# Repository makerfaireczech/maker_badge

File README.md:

# Maker badge
The Maker badge board is the official badge board for Maker Faire's in the Czech republic. The main purpose is to show visitors/exhibitors name and/or project, but the secondary goal is to have at each Maker Faire some interactive game so people can have more fun at the time of the visit.

This board supports [Arduino](https://github.com/espressif/arduino-esp32) and [CircuitPython](https://learn.adafruit.com/welcome-to-circuitpython) platform. 

CircuitPython will be **primary** platform for this board because it is very easy to use, and anybody who will buy a board at some Maker Fair should be able very easily change (at least) her/his name on the display, so anybody knows the name of the person when they start chatting about something.  

I will try to add as many examples for both platforms, as I could, but I already saw few very interesting projects.

## How to use this board in 5 steps:  

1) Connect USB-C cable to the board and turn it on. 
Either use a slide switch (top = OFF, down = ON) or move the jumper to the middle pins. This depends on the version which you have. 

2) Locate drive name "**Circuitpy**" and open **code.py** in some text editor. 
We recommend using **Mu editor**, but even Notepad will work. 

3) Find a line where is **"Jmeno"** (Name), **"Prijmeni"** (Surname), **"Firma/Projekt"** (Company/Project) and change it to whatever suit your need. 
There is yet no "auto aligning", so you have to also change X & Y coordinates for particular text. 

4) Save it via **CTRL+S/CMD+S** or you application menu for that. If the screen does not refresh, push the RESET button. 

5) Unplug the USB cable, put the strap around your neck, and wear it with pride. 

## Board version

There are currently following revisions of the board:

- rev. A : this version was distributed by me and it was using **212 x 104 px** e-ink display with UC8151D driver
- rev. B : this board was assembled by me for Maker Faire Prague 2022 and it was using **250 x 122 px** e-ink display with SSD1680 driver from Make More. It contains the same type of components as rev. A .  
- rev. C (with rev. B markings at the back): this board was assembled by PCBWay and it was using **250 x 122 px** e-ink display with SSD1680 driver from Make More. Some of the components are different because the original parts were not available due to chip shortage. These boards were distributed between Maker Faire Brno 2022 (22 - 23/10/2022) and Maker Faire Prague 2023 (10 - 11/6/2023).
- rev. D : this board was assembled by PCBWay and it contains these changes:
	- slide switch for power control instead of jumper over pins
	- transistor at e-ink display power line to save power 
	- transistor at resistor divider for battery measuring
	- CR2032 holder was removed to save the cost of the board

	These boards were distributed at Maker Faire Prague 2023 (10 - 11/6/2023) and onwards.

## Where can you buy it? 

[Makermarket](https://www.makermarket.cz/maker-badge)

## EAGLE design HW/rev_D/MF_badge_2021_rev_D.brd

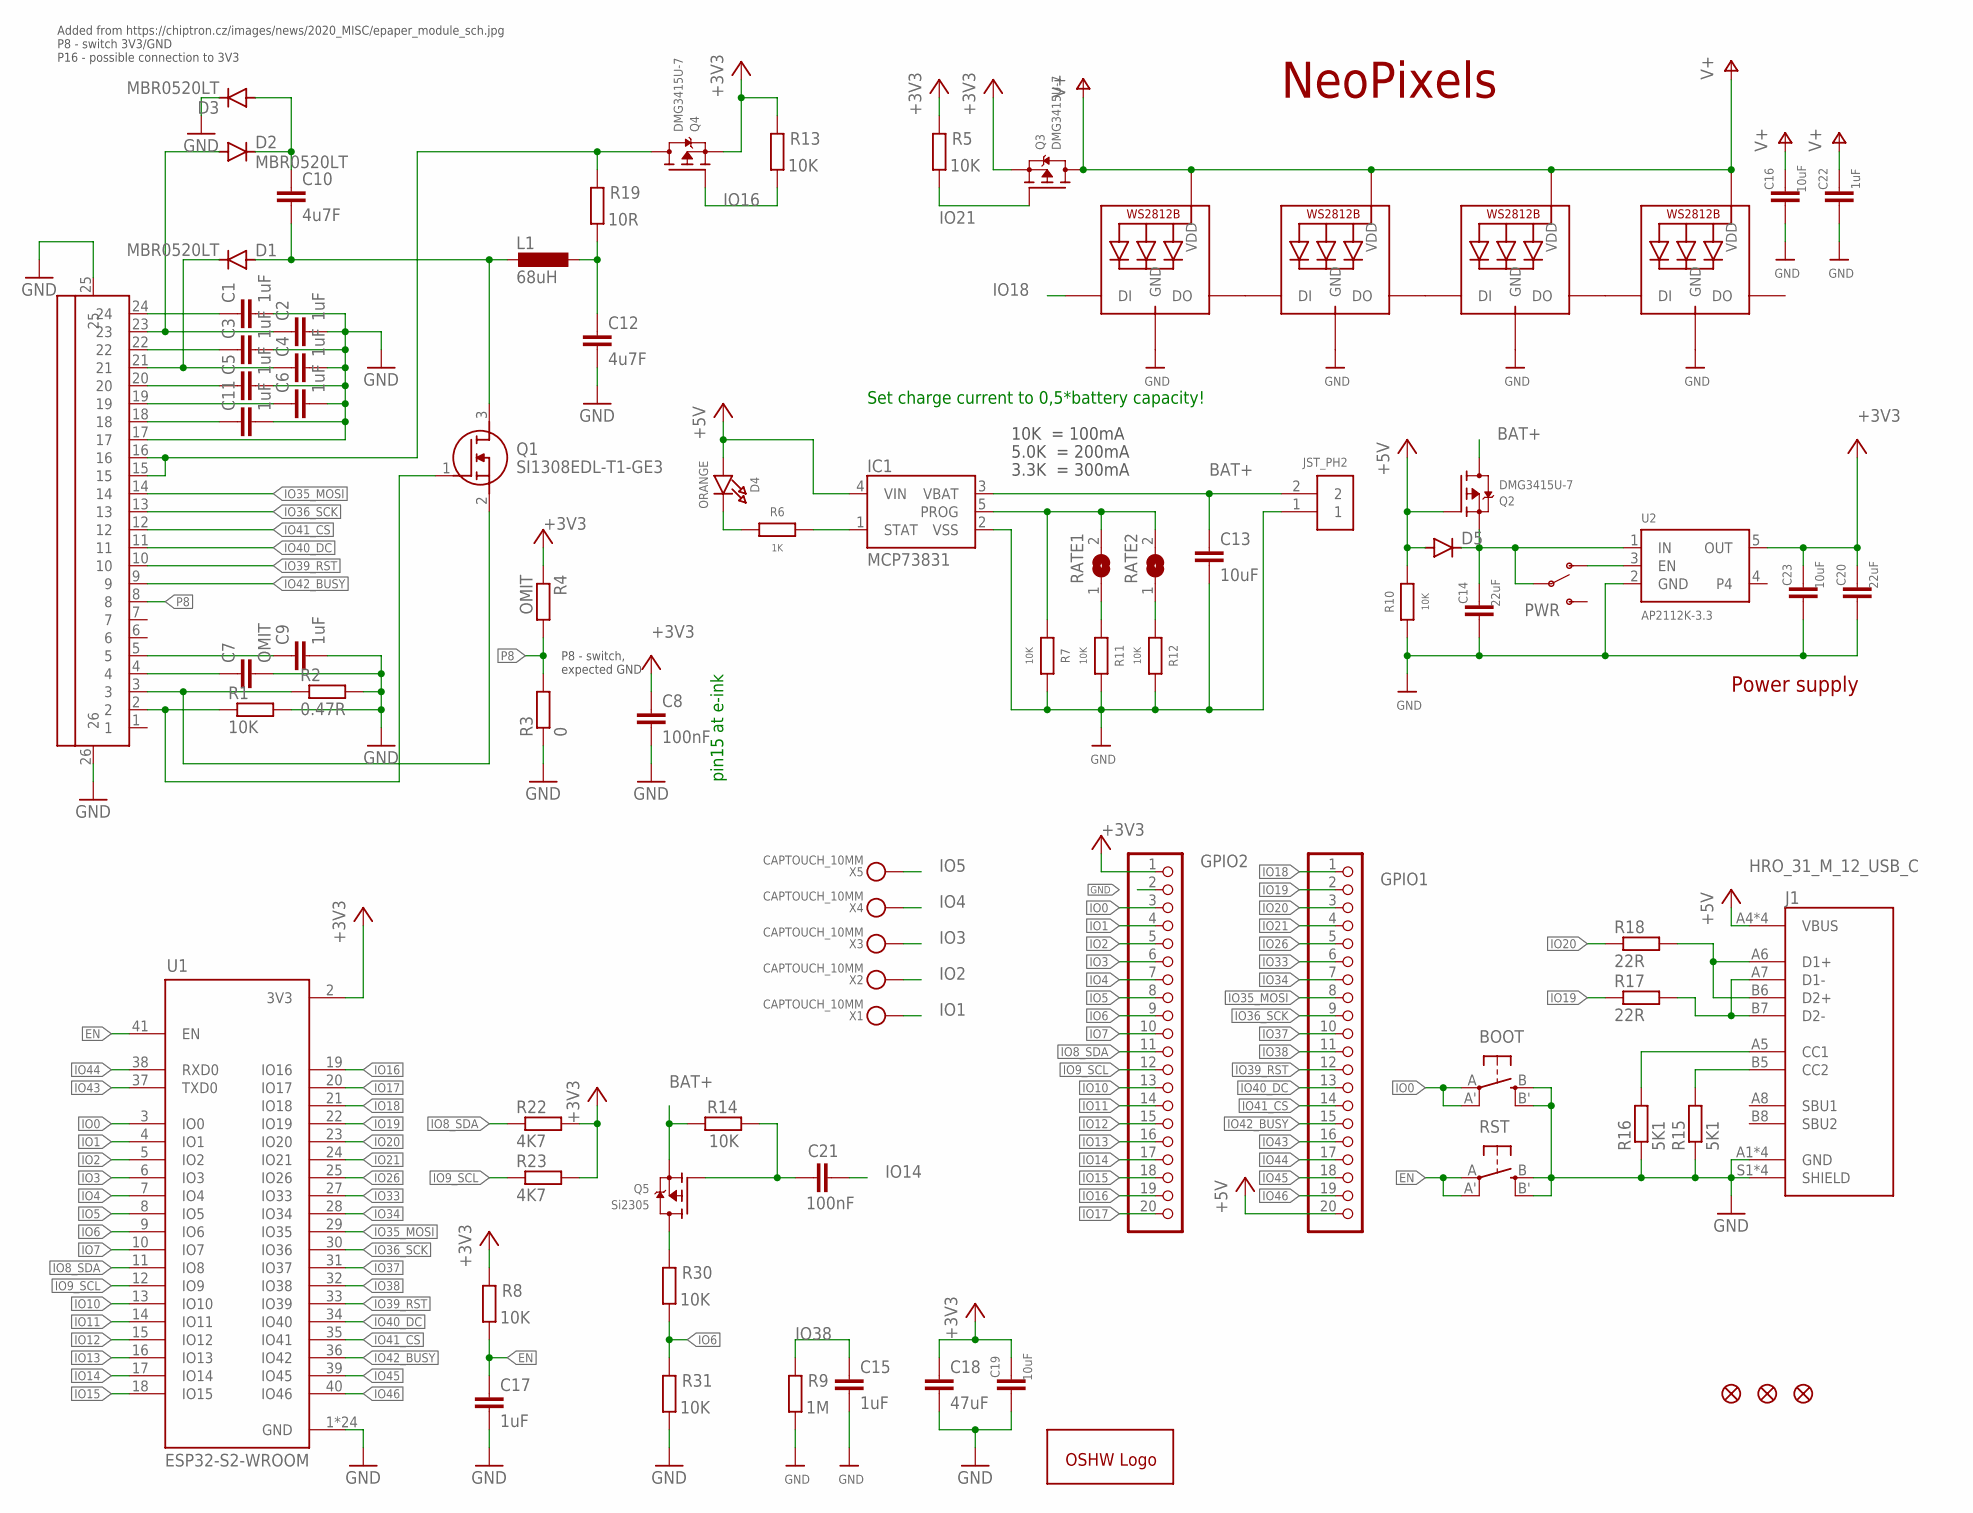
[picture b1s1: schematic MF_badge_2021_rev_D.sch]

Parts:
BOOT: BUTTON_KMR2_4.6X2.8
C1, C2, C3, C4, C5, C6, C9, C11, C15, C17, C22: 1uF; C0805
C7: OMIT; C0805
C8, C21: 100nF; C0805
C10, C12: 4u7F; C0805
C13, C16, C19, C23: 10uF; C0805
C14, C20: 22uF; C0805
C18: 47uF; C0805
D1, D2, D3, D5: MBR0520LT; SOD123
D4: ORANGE; CHIPLED_0805_NOOUTLINE
FID1, FID2, FID3: FIDUCIAL""; FIDUCIAL_1MM
GOLD_ORB_SM1: OSHWLOGO_; OSHW_5MM_LOGO
GPIO1, GPIO2: PINHD-1X20; 1X20
IC1: MCP73831; SOT95P290X120-5
J1: HRO_31_M_12_USB_C
L1: 68uH; L4532P
LED2, LED3, LED4, LED5: WS2812B5050; WS2812B
PWR: SWITCH-SPDT-SMD-RIGHT-ANGLE; SWITCH_SPST_SMD_A
Q1: SI1308EDL-T1-GE3; SOT65P210X110-3N
Q2, Q3, Q4: DMG3415U-7; SOT23-R
Q5: Si2305; SOT23-R
R1, R5, R7, R8, R10, R11, R12, R13, R14, R30, R31: 10K; R0805
R2: 0.47R; R0805
R3: 0; R0805
R4: OMIT; R0805
R6: 1K; R0805
R9: 1M; R0805
R15, R16: 5K1; R0805
R17, R18: 22R; R0805
R19: 10R; R0805
R22, R23: 4K7; R0805
RATE1, RATE2: SOLDERJUMPER; SOLDERJUMPER_ARROW_NOPASTE
RST: BUTTON_KMR2_4.6X2.8
U1: ESP32-S2-WROOM; XCVR_ESP32-S2-WROOM
U2: AP2112K-3.3; SOT23-5
U$1: 2.13_EINK
U$8: JST_PH2; JSTPH2
X1, X2, X3, X4, X5: CAPTOUCH_10MM; CAPTOUCH_6X9MM

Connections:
+3V3: C8.1, C18.1, C19.1, C20.1, C23.1, GPIO2.1, Q3.2 (S), Q4.2 (S), R4.1, R5.2, R8.2, R13.2, R22.2, R23.2, U1.2 (3V3), U2.5 (OUT)
+5V: D4.A, D5.A, GPIO1.20, IC1.4 (VIN), J1.A4 (VBUS), J1.A9 (VBUS), J1.B4 (VBUS), J1.B9 (VBUS), Q2.1 (G), R10.2
BAT+: C13.1, IC1.3 (VBAT), Q2.3 (D), Q5.2 (S), R14.2, U$8.2
D+_CON: J1.A6 (D1+), J1.B6 (D2+), R18.2
D-_CON: J1.A7 (D1-), J1.B7 (D2-), R17.2
EN: C17.1, R8.1, RST.A, RST.A' (P1), U1.41 (EN)
GND: BOOT.B (S), BOOT.B' (S1), C1.2, C2.2, C3.2, C4.2, C5.2, C6.2, C7.2, C8.2, C9.2, C11.2, C12.2, C13.2, C14.2, C15.2, C16.2, C17.2, C18.2, C19.2, C20.2, C22.2, C23.2, D3.C, GPIO2.2, IC1.2 (VSS), J1.A1 (GND), J1.A12 (GND), J1.B1 (GND), J1.B12 (GND), J1.S1 (SHIELD), J1.S2 (SHIELD), J1.S3 (SHIELD), J1.S4 (SHIELD), LED2.3-GND (GND), LED3.3-GND (GND), LED4.3-GND (GND), LED5.3-GND (GND), R1.2, R2.2, R3.1, R7.2, R9.1, R10.1, R11.2, R12.2, R15.1, R16.1, R31.1, RST.B (S), RST.B' (S1), U1.1 (GND), U1.26 (GND), U1.42 (GND), U1.43.1 (GND), U1.43.2 (GND), U1.43.3 (GND), U1.43.4 (GND), U1.43.5 (GND), U1.43.6 (GND), U1.43.7 (GND), U1.43.8 (GND), U1.43.9 (GND), U1.43.10 (GND), U1.43.11 (GND), U1.43.12 (GND), U1.43.13 (GND), U1.43.14 (GND), U1.43.15 (GND), U1.43.16 (GND), U1.43.17 (GND), U1.43.18 (GND), U1.43.19 (GND), U1.43.20 (GND), U1.43.21 (GND), U2.2 (GND), U$1.17, U$1.25, U$1.26, U$8.1
IO0: BOOT.A, BOOT.A' (P1), GPIO2.3, U1.3 (IO0)
IO1: GPIO2.4, U1.4 (IO1), X1.P$1
IO2: GPIO2.5, U1.5 (IO2), X2.P$1
IO3: GPIO2.6, U1.6 (IO3), X3.P$1
IO4: GPIO2.7, U1.7 (IO4), X4.P$1
IO5: GPIO2.8, U1.8 (IO5), X5.P$1
IO6: GPIO2.9, R30.1, R31.2, U1.9 (IO6)
IO7: GPIO2.10, U1.10 (IO7)
IO8_SDA: GPIO2.11, R22.1, U1.11 (IO8)
IO9_SCL: GPIO2.12, R23.1, U1.12 (IO9)
IO10: GPIO2.13, U1.13 (IO10)
IO11: GPIO2.14, U1.14 (IO11)
IO12: GPIO2.15, U1.15 (IO12)
IO13: GPIO2.16, U1.16 (IO13)
IO14: C21.2, GPIO2.17, U1.17 (IO14)
IO15: GPIO2.18, U1.18 (IO15)
IO16: GPIO2.19, Q4.1 (G), R13.1, U1.19 (IO16)
IO17: GPIO2.20, U1.20 (IO17)
IO18: GPIO1.1, LED2.4-DIN (DI), U1.21 (IO18)
IO19: GPIO1.2, R17.1, U1.22 (IO19)
IO20: GPIO1.3, R18.1, U1.23 (IO20)
IO21: GPIO1.4, Q3.1 (G), R5.1, U1.24 (IO21)
IO26: GPIO1.5, U1.25 (IO26)
IO33: GPIO1.6, U1.27 (IO33)
IO34: GPIO1.7, U1.28 (IO34)
IO35_MOSI: GPIO1.8, U1.29 (IO35), U$1.14
IO36_SCK: GPIO1.9, U1.30 (IO36), U$1.13
IO37: GPIO1.10, U1.31 (IO37)
IO38: C15.1, GPIO1.11, R9.2, U1.32 (IO38)
IO39_RST: GPIO1.12, U1.33 (IO39), U$1.10
IO40_DC: GPIO1.13, U1.34 (IO40), U$1.11
IO41_CS: GPIO1.14, U1.35 (IO41), U$1.12
IO42_BUSY: GPIO1.15, U1.36 (IO42), U$1.9
IO43: GPIO1.16, U1.37 (TXD0)
IO44: GPIO1.17, U1.38 (RXD0)
IO45: GPIO1.18, U1.39 (IO45)
IO46: GPIO1.19, U1.40 (IO46)
unnamed: C1.1, U$1.24
unnamed: C2.1, D2.A, U$1.23
unnamed: C3.1, U$1.22
unnamed: C4.1, D1.C, U$1.21
unnamed: C5.1, U$1.20
unnamed: C6.1, U$1.19
unnamed: C11.1, U$1.18
unnamed: IC1.1 (STAT), R6.2
unnamed: C14.1, D5.C, PWR.2, Q2.2 (S), U2.1 (IN)
unnamed: Q1.2 (S), R2.1, U$1.3
unnamed: C9.1, U$1.5
unnamed: C7.1, U$1.4
unnamed: Q1.1 (G), R1.1, U$1.2
unnamed: D4.C, R6.1
unnamed: C10.1, D2.C, D3.A
unnamed: LED2.2-DOUT (DO), LED3.4-DIN (DI)
unnamed: PWR.1 (O), U2.3 (EN)
unnamed: C10.2, D1.A, L1.2, Q1.3 (D)
unnamed: R11.1, RATE1.1
unnamed: R12.1, RATE2.1
unnamed: LED4.2-DOUT (DO), LED5.4-DIN (DI)
unnamed: J1.B5 (CC2), R15.2
unnamed: J1.A5 (CC1), R16.2
unnamed: LED3.2-DOUT (DO), LED4.4-DIN (DI)
unnamed: Q4.3 (D), R19.2, U$1.15, U$1.16
unnamed: C12.1, L1.1, R19.1
unnamed: Q5.3 (D), R30.2
unnamed: C21.1, Q5.1 (G), R14.1
P8: R3.2, R4.2, U$1.8
PROG: IC1.5 (PROG), R7.1, RATE1.2, RATE2.2
V+: C16.1, C22.1, LED2.1-VDD (VDD), LED3.1-VDD (VDD), LED4.1-VDD (VDD), LED5.1-VDD (VDD), Q3.3 (D)

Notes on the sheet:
P8 - switch, expected GND
Added from https://chiptron.cz/images/news/2020_MISC/epaper_module_sch.jpg P8 - switch 3V3/GND P16 - possible connection to 3V3
10K = 100mA
5.0K = 200mA
3.3K = 300mA
Set charge current to 0,5*battery capacity!
Power supply
pin15 at e-ink
NeoPixels

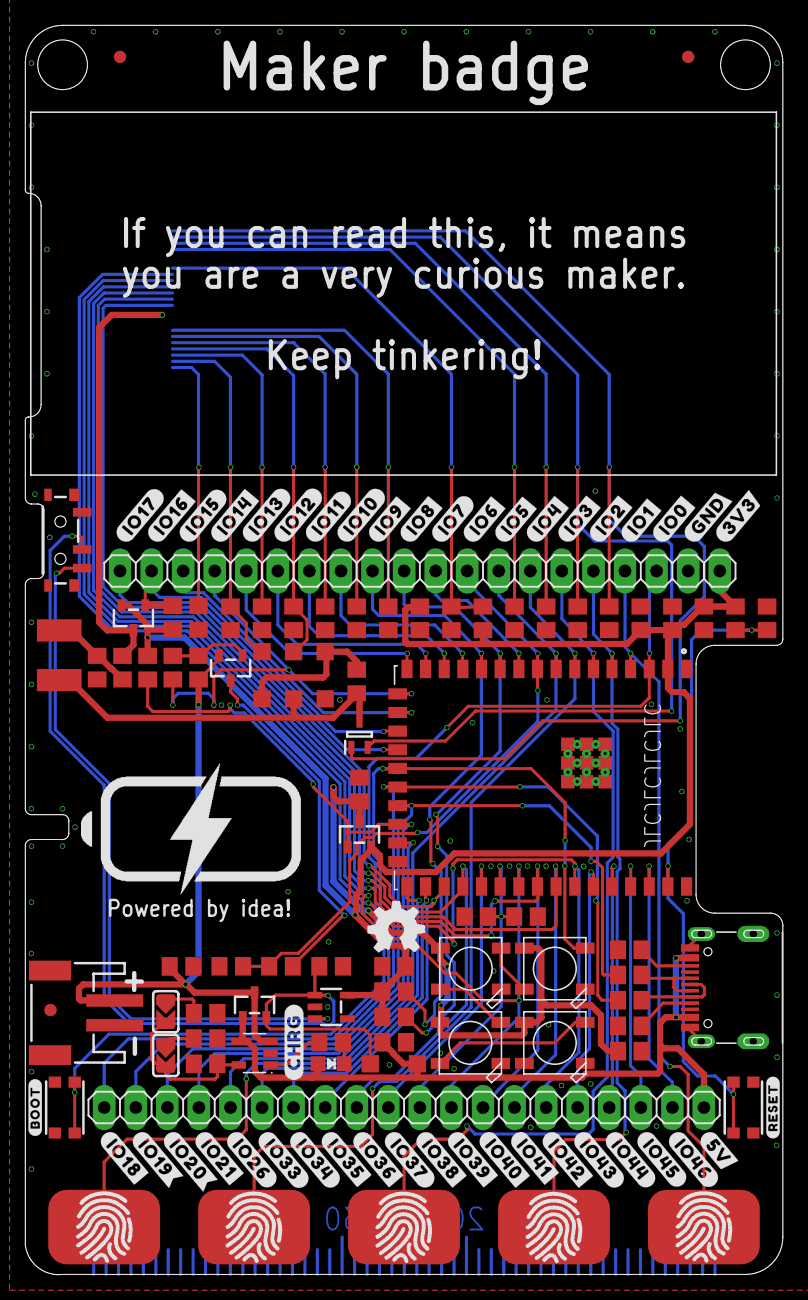
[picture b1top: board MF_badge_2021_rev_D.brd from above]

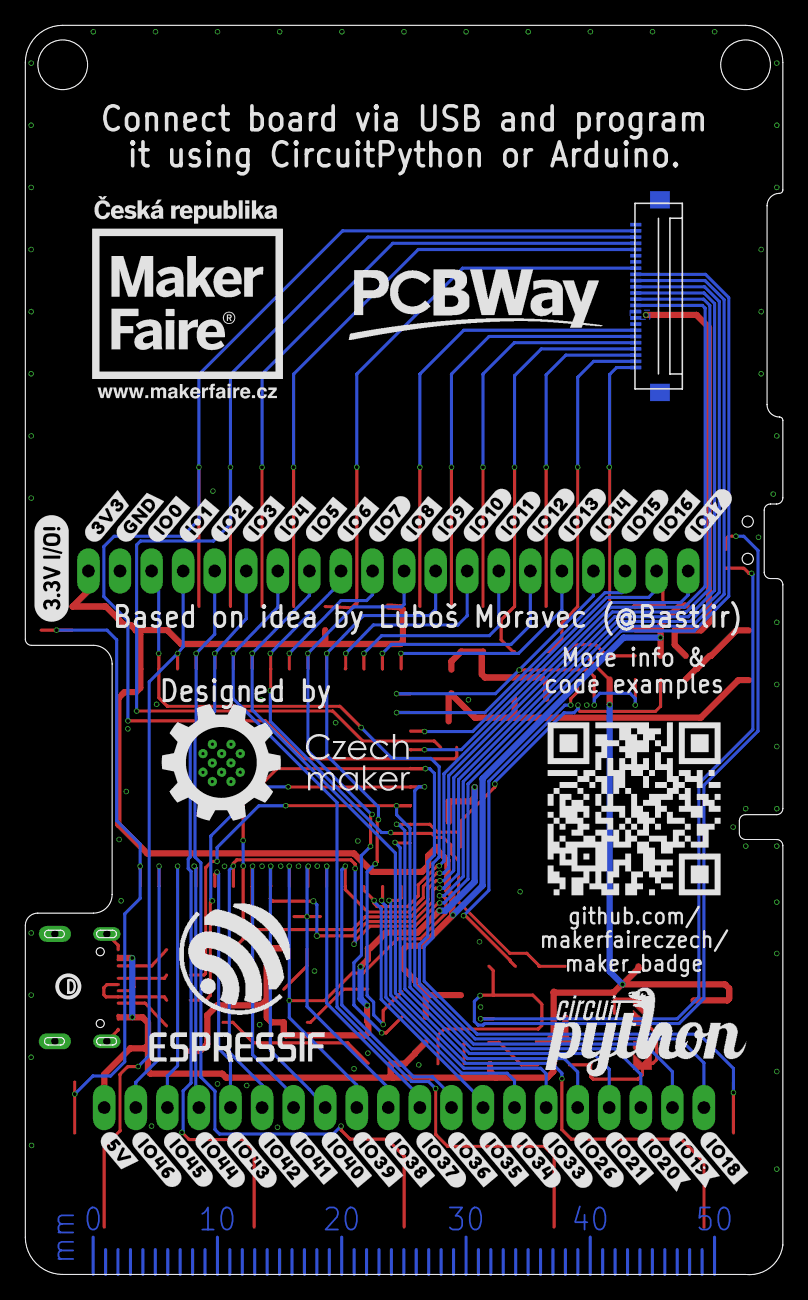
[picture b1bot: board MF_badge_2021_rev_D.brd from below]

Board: 2 copper layers, 61.0 x 100.5 mm, 167 parts (41 on the bottom side), 75 nets.

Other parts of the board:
U$2, U$92: #IO43#0
U$3, U$93: #IO44#0
U$4, U$33: #IO17#0
U$6, U$34: #IO16#0
U$7: #BOOT#0
U$9: #RESET#0
U$10: PCBFEAT-REV-040
U$12: #CHRG#0
U$16, U$77: #IO18#0
U$17, U$78: #IO19#0
U$18, U$79: #IO20#0
U$19, U$80: #IO21#0
U$20, U$81: #IO26#0
U$21, U$82: #IO33#0
U$22, U$83: #IO34#0
U$23, U$84: #IO35#0
U$24, U$85: #IO36#0
U$25, U$87: #IO38#0
U$26, U$86: #IO37#0
U$27, U$88: #IO39#0
U$28, U$89: #IO40#0
U$29, U$90: #IO41#0
U$30, U$91: #IO42#0
U$31, U$94: #IO45#0
U$32, U$95: #IO46#0
U$35, U$57: #IO15#0
U$37, U$58: #IO14#0
U$38, U$59: #IO13#0
U$39, U$60: #IO12#0
U$40, U$65: #IO11#0
U$41, U$66: #IO10#0
U$42, U$67: #IO9#0
U$43, U$68: #IO8#0
U$44, U$69: #IO7#0
U$45, U$70: #IO6#0
U$46, U$71: #IO5#0
U$47, U$72: #IO4#0
U$48, U$73: #IO3#0
U$49, U$74: #IO2#0
U$50, U$75: #IO1#0
U$51, U$76: #IO0#0
U$96, U$100: #GND#0
U$97, U$101: #3V3#0
U$98, U$99: #5V#0

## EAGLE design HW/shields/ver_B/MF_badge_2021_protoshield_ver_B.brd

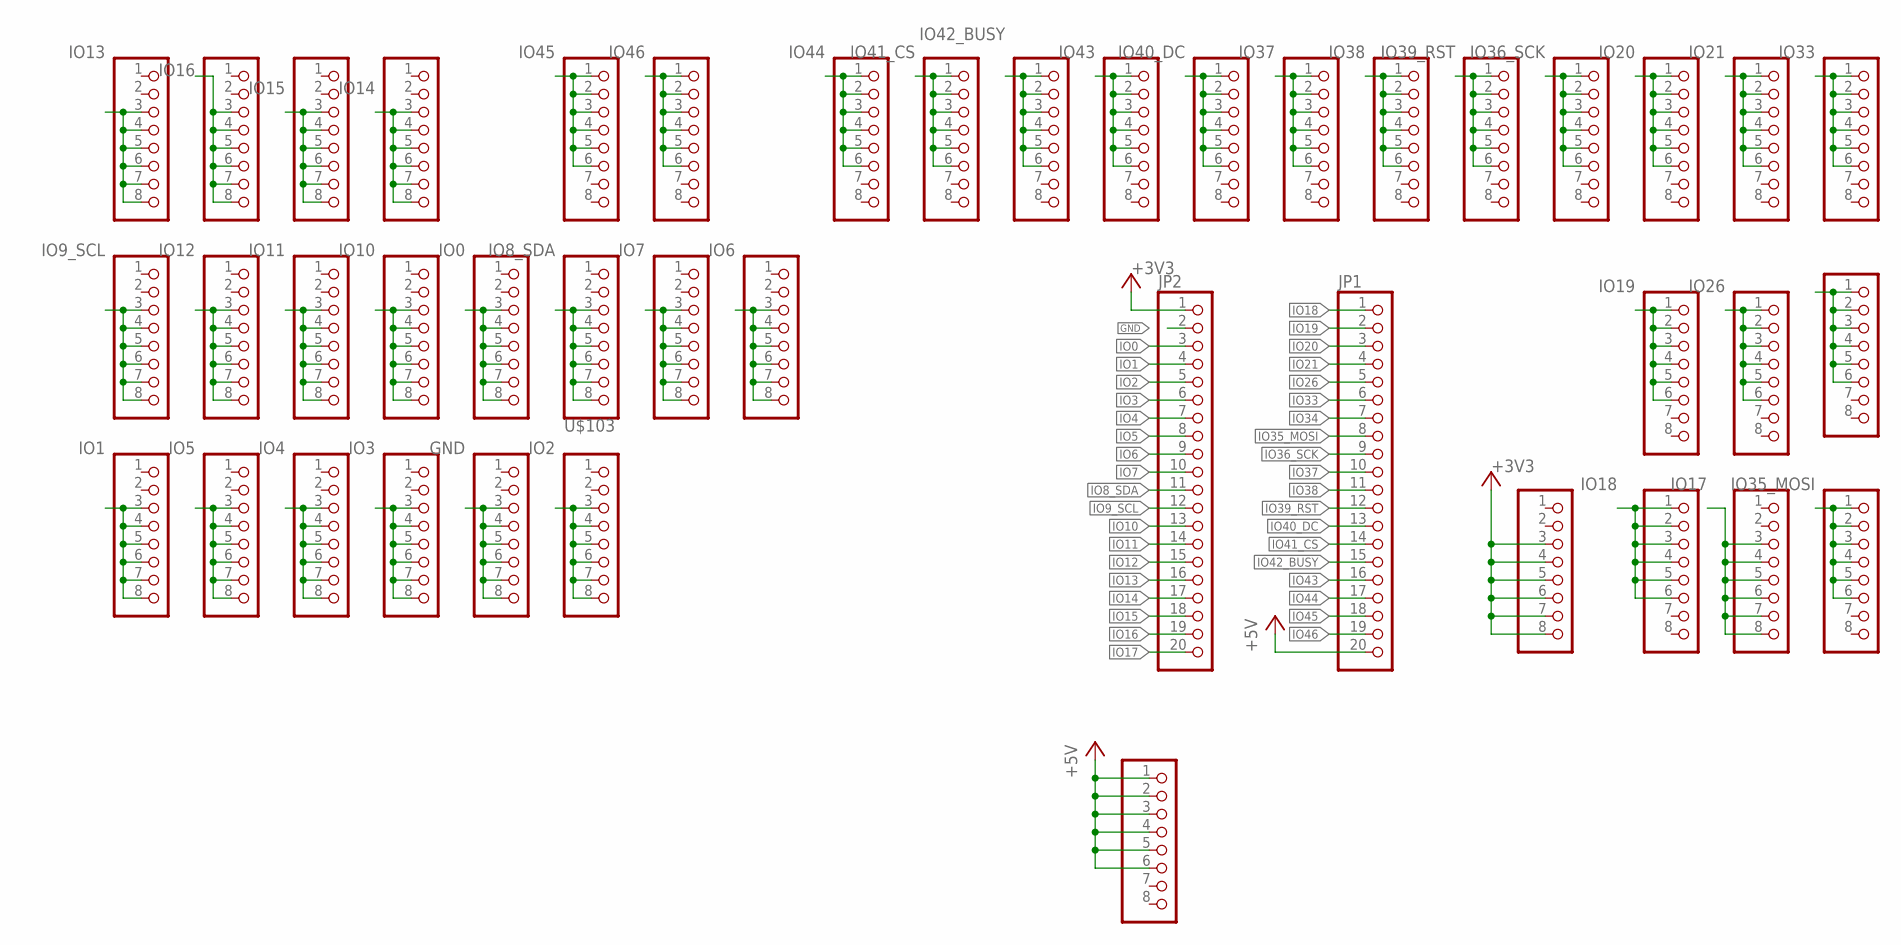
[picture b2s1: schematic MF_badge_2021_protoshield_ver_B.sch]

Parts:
JP1, JP2: PINHD-1X20_CLEANBIG; 1X20-CLEANBIG
U$1, U$5, U$7, U$8, U$9, U$10, U$11, U$12, U$13, U$14, U$15, U$36, U$52, U$53, U$54, U$55, U$56, U$61, U$62, U$63, U$64, U$102, U$103, U$104, U$105, U$106, U$107, U$108, U$109, U$110, U$111, U$112, U$113, U$114, U$115, U$116, U$117, U$118, U$119, U$120: PINHD-1X8CLEANBIG; 1X08-CLEANBIG

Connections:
+3V3: JP2.1, U$1.3, U$1.4, U$1.5, U$1.6, U$1.7, U$1.8
+5V: JP1.20, U$102.1, U$102.2, U$102.3, U$102.4, U$102.5, U$102.6
GND: JP2.2, U$120.3, U$120.4, U$120.5, U$120.6, U$120.7, U$120.8
IO0: JP2.3, U$115.3, U$115.4, U$115.5, U$115.6, U$115.7, U$115.8
IO1: JP2.4, U$119.3, U$119.4, U$119.5, U$119.6, U$119.7, U$119.8
IO2: JP2.5, U$103.3, U$103.4, U$103.5, U$103.6, U$103.7, U$103.8
IO3: JP2.6, U$118.3, U$118.4, U$118.5, U$118.6, U$118.7, U$118.8
IO4: JP2.7, U$117.3, U$117.4, U$117.5, U$117.6, U$117.7, U$117.8
IO5: JP2.8, U$116.3, U$116.4, U$116.5, U$116.6, U$116.7, U$116.8
IO6: JP2.9, U$114.3, U$114.4, U$114.5, U$114.6, U$114.7, U$114.8
IO7: JP2.10, U$113.3, U$113.4, U$113.5, U$113.6, U$113.7, U$113.8
IO8_SDA: JP2.11, U$112.3, U$112.4, U$112.5, U$112.6, U$112.7, U$112.8
IO9_SCL: JP2.12, U$111.3, U$111.4, U$111.5, U$111.6, U$111.7, U$111.8
IO10: JP2.13, U$110.3, U$110.4, U$110.5, U$110.6, U$110.7, U$110.8
IO11: JP2.14, U$109.3, U$109.4, U$109.5, U$109.6, U$109.7, U$109.8
IO12: JP2.15, U$108.3, U$108.4, U$108.5, U$108.6, U$108.7, U$108.8
IO13: JP2.16, U$107.3, U$107.4, U$107.5, U$107.6, U$107.7, U$107.8
IO14: JP2.17, U$106.3, U$106.4, U$106.5, U$106.6, U$106.7, U$106.8
IO15: JP2.18, U$105.3, U$105.4, U$105.5, U$105.6, U$105.7, U$105.8
IO16: JP2.19, U$104.3, U$104.4, U$104.5, U$104.6, U$104.7, U$104.8
IO17: JP2.20, U$7.3, U$7.4, U$7.5, U$7.6, U$7.7, U$7.8
IO18: JP1.1, U$5.1, U$5.2, U$5.3, U$5.4, U$5.5, U$5.6
IO19: JP1.2, U$8.1, U$8.2, U$8.3, U$8.4, U$8.5, U$8.6
IO20: JP1.3, U$9.1, U$9.2, U$9.3, U$9.4, U$9.5, U$9.6
IO21: JP1.4, U$10.1, U$10.2, U$10.3, U$10.4, U$10.5, U$10.6
IO26: JP1.5, U$11.1, U$11.2, U$11.3, U$11.4, U$11.5, U$11.6
IO33: JP1.6, U$12.1, U$12.2, U$12.3, U$12.4, U$12.5, U$12.6
IO34: JP1.7, U$13.1, U$13.2, U$13.3, U$13.4, U$13.5, U$13.6
IO35_MOSI: JP1.8, U$14.1, U$14.2, U$14.3, U$14.4, U$14.5, U$14.6
IO36_SCK: JP1.9, U$15.1, U$15.2, U$15.3, U$15.4, U$15.5, U$15.6
IO37: JP1.10, U$36.1, U$36.2, U$36.3, U$36.4, U$36.5, U$36.6
IO38: JP1.11, U$52.1, U$52.2, U$52.3, U$52.4, U$52.5, U$52.6
IO39_RST: JP1.12, U$53.1, U$53.2, U$53.3, U$53.4, U$53.5, U$53.6
IO40_DC: JP1.13, U$54.1, U$54.2, U$54.3, U$54.4, U$54.5, U$54.6
IO41_CS: JP1.14, U$55.1, U$55.2, U$55.3, U$55.4, U$55.5, U$55.6
IO42_BUSY: JP1.15, U$56.1, U$56.2, U$56.3, U$56.4, U$56.5, U$56.6
IO43: JP1.16, U$61.1, U$61.2, U$61.3, U$61.4, U$61.5, U$61.6
IO44: JP1.17, U$62.1, U$62.2, U$62.3, U$62.4, U$62.5, U$62.6
IO45: JP1.18, U$63.1, U$63.2, U$63.3, U$63.4, U$63.5, U$63.6
IO46: JP1.19, U$64.1, U$64.2, U$64.3, U$64.4, U$64.5, U$64.6

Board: 2 copper layers, 42 parts (0 on the bottom side), 40 nets, no tracks yet.

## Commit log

2023-03-02 Update
    - removed CR2032 battery holder
    - changed battery measuring circuit to save power
    - add N-MOSFET to control 3V3 to e-ink displey
    - changed QR to match new project address
2023-03-02 Update
    - schematic cleanup
    - power supply layout optimization
    - changed some R and C values
    - add hole for battery holder
2023-03-06 Update
    - bigger slot for battery holder
    - GND stitching for better RF
2023-03-09 Add CPY example for rev.A
2023-03-09 Update
    - add pin to drive Q4
    - changed pin labels to match reality
    - add .gitignore file
2023-03-09 Update MF_badge_2021_rev_D.sch
    - forget to add it in previous commit
2023-03-20 Verified design files for rev.D
2023-03-24 Add ESPRESSIF logo
2023-04-02 Error fix for 3V3 line at e-ink display
2023-04-02 Moved 3V3 for e-ink power pins before R19
2023-06-11 Update
    - added schematics for all versions
    - added protoshield files
    - added files for rev. D
    - README update
    - removed unnecessary files
2023-06-12 added example for logo from BMP file
2023-07-10 Update
    - add simple Arduino example for rev. D
    - add bitmap + battery reading example for CircuitPython
2023-07-23 docs: fix outdated README.md
2023-07-23 docs: remove wiki link from README.md as wiki was not transferred from previous repository
2023-07-23 docs: fix typo in README.md
2023-10-02 Update
    - comment update in Badge_rev_D_full_test.ino
    - typo fix in name of the skecth for simple text example
    - update Maker_badge_simple_text.ino example to work with rev.D version of the board
2024-05-12 Update README.md
    - add links
    - changed the grammar of the sentences

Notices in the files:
parts and their libraries:
microbuilder: This work is placed in the public domain, and may be freely used for commercial and non-commercial work with the following conditions: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
